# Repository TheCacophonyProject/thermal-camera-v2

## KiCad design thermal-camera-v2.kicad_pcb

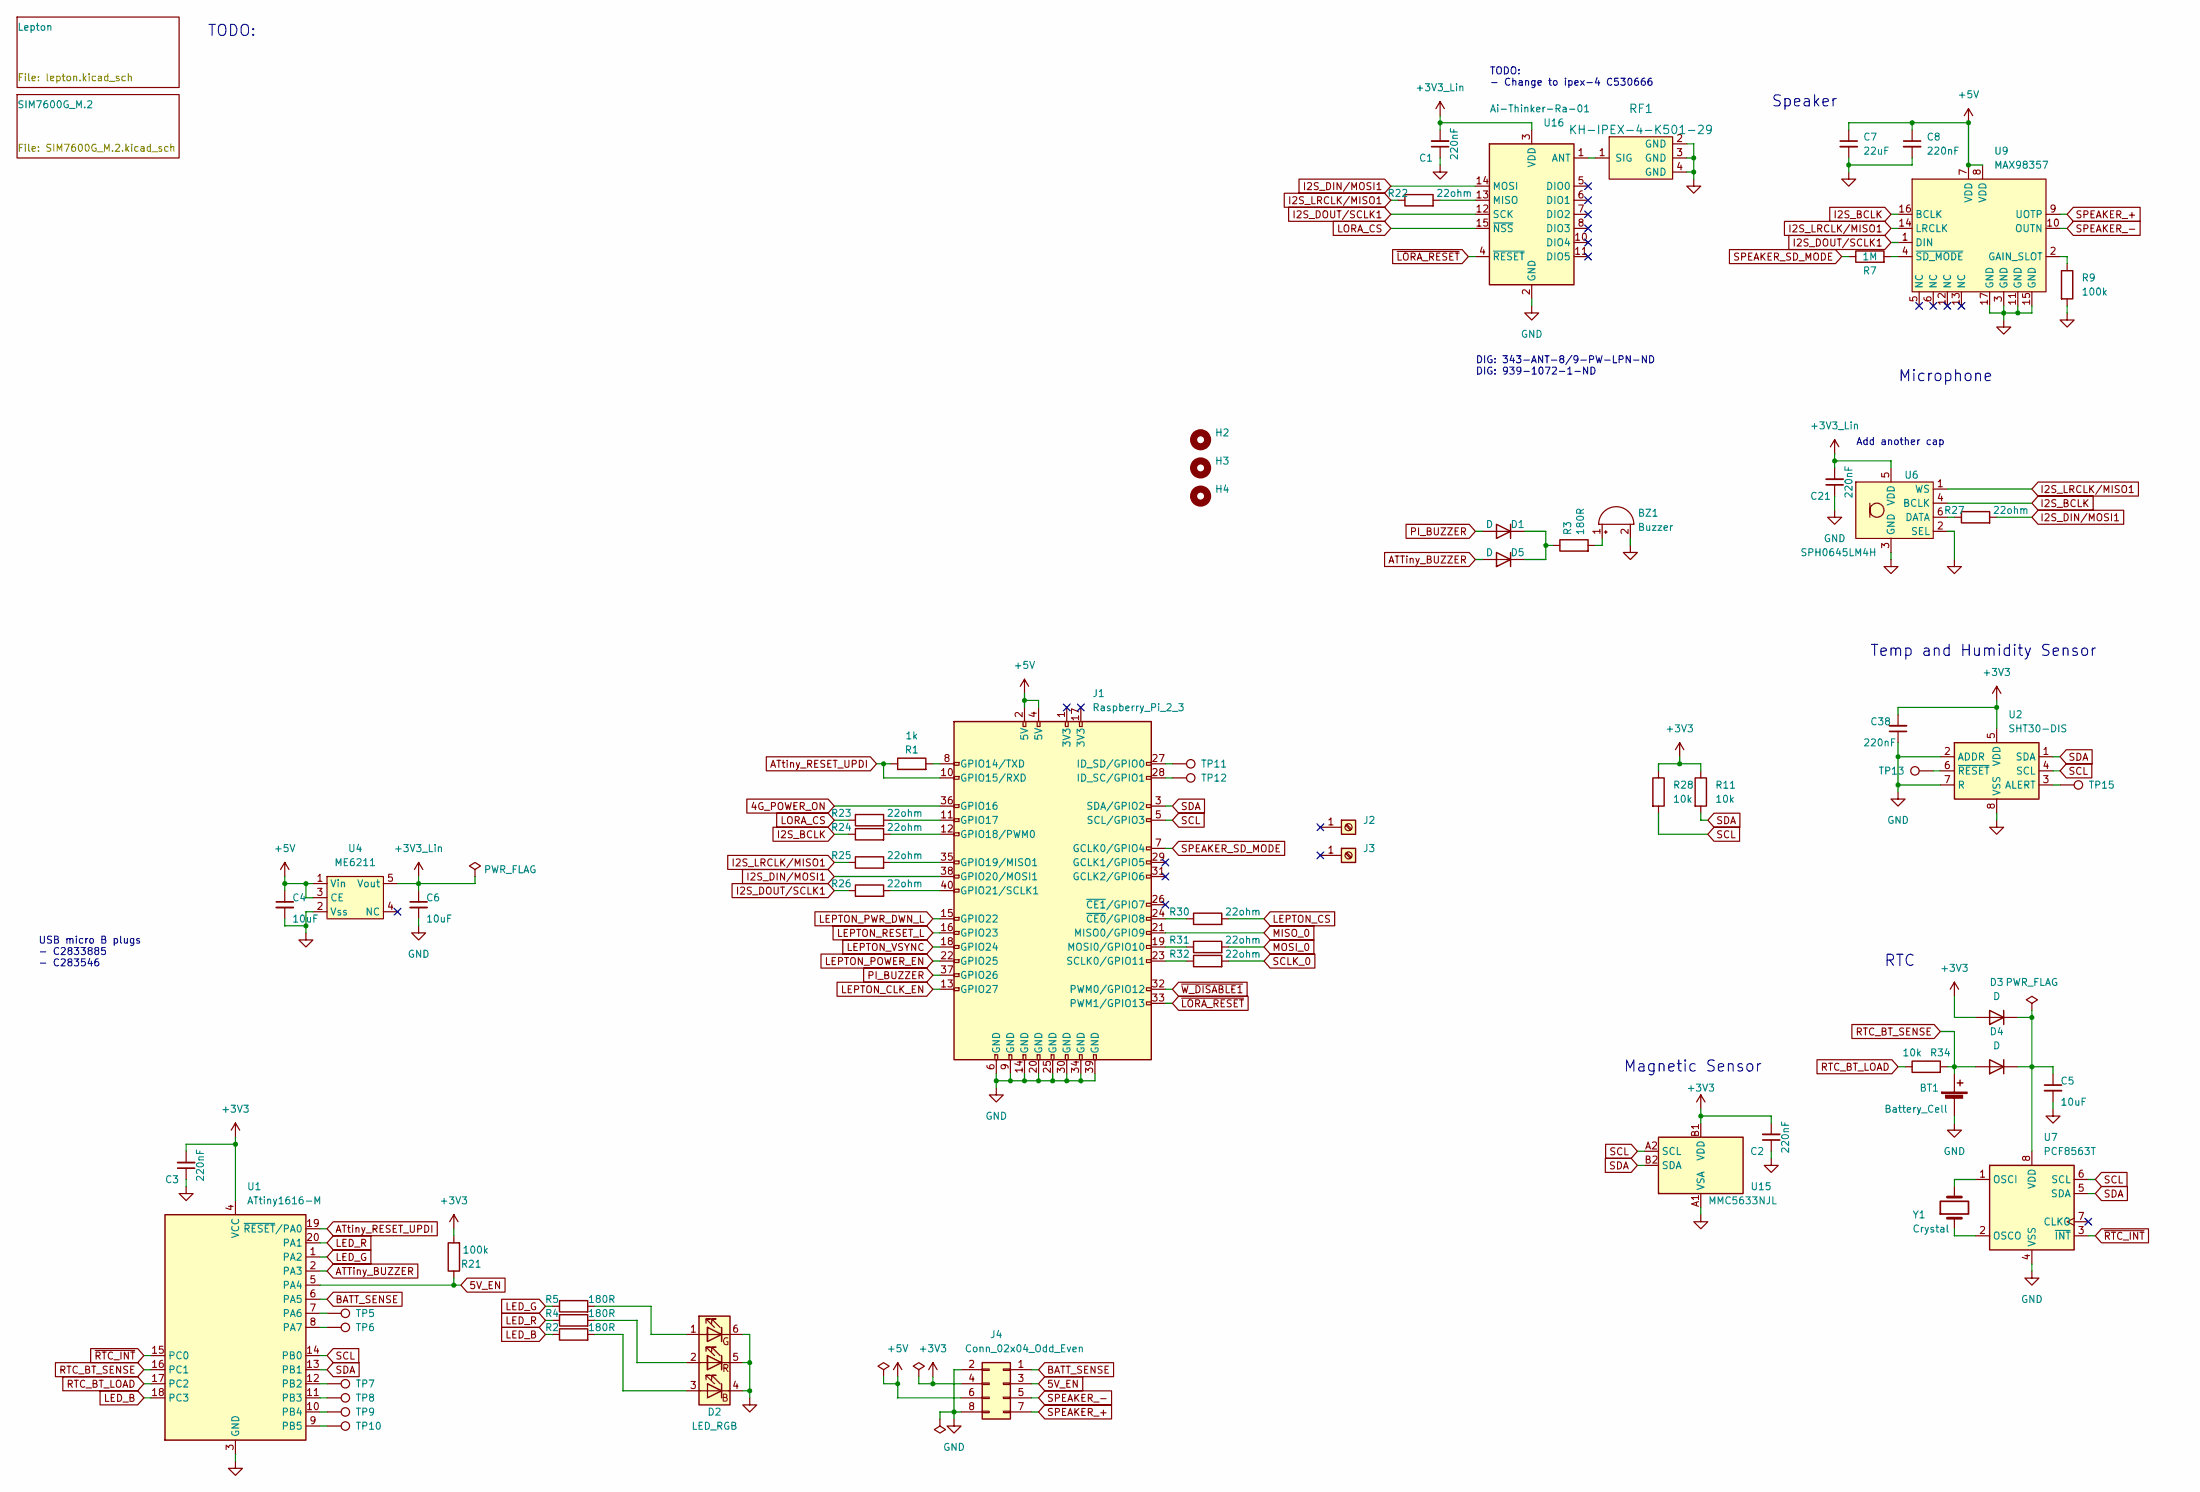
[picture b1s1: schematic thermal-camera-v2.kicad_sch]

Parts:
BT1: Battery_Cell; CR1220; LCSC C969906
BZ1: Buzzer; BUZ-TH_BD9.0-P5.00-D0.6-FD; LCSC C96102
C1, C2, C3, C8, C21, C38: 220nF; C_0402_1005Metric; LCSC C16772
C4, C5, C6: 10uF; C_0603_1608Metric; LCSC C19702
C7: 22uF; C_0603_1608Metric; LCSC C86295
D1, D3, D4, D5: D; D_SOD-523; LCSC C668989
D2: LED_RGB; LED-SMD_6PIN-L1.60-W1.50-BL-RD; LCSC C375568
H2, H3, H4: MountingHole; Mouning_Hole_M3
J1: Raspberry_Pi_2_3; RPi_2_W_SMD; LCSC C3975165
J2, J3: Screw_Terminal_M2_L10; SMD_NUT_D5.6-HD3.6-L10.0; LCSC C2928171
J4: Conn_02x04_Odd_Even; power-pcb; LCSC C124386
R1: 1k; R_0402_1005Metric; LCSC C11702
R2, R3, R4, R5: 180R; R_0402_1005Metric; LCSC C38941
R7: 1M; R_0603_1608Metric; LCSC C22935
R9, R21: 100k; R_0402_1005Metric; LCSC C25741
R11, R28, R34: 10k; R_0402_1005Metric; LCSC C25744
R22, R23, R24, R25, R26, R27, R30, R31, R32: 22ohm; R_0402_1005Metric; LCSC C25092
RF1: KH-IPEX-4-K501-29; IPEX4-SMD_4P-L1.8-W1.7-LS2.0-L_KH-IPEX4-2020; LCSC C530666
TP5, TP6, TP7, TP8, TP9, TP10, TP13, TP15: TestPoint; TP_PAD
TP11, TP12: TestPoint; TP
U1: ATtiny1616-M; VQFN-20-1EP_3x3mm_P0.4mm_EP1.7x1.7mm; LCSC C507118
U2: SHT30-DIS; Sensirion_DFN-8-1EP_2.5x2.5mm_P0.5mm_EP1.1x1.7mm; LCSC C77361
U4: ME6211; SOT-23-5; LCSC C82942
U6: SPH0645LM4H; MIC_SPH0645LM4H-B; LCSC C2686054
U7: PCF8563T; SOIC-8_3.9x4.9mm_P1.27mm; LCSC C7440
U9: MAX98357; TQFN-16-1EP_3x3mm_P0.5mm_EP1.6x1.6mm; LCSC C910544
U15: MMC5633NJL; WLP-4_0.86x0.86mm_P0.4mm; LCSC C404328
U16: Ai-Thinker-Ra-01; WIRELM-SMD_RA-01H; LCSC C503593
Y1: Crystal; Crystal_SMD_3215-2Pin_3.2x1.5mm; LCSC C32346

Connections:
4G_POWER_ON: J1.36 (GPIO16); also elsewhere on the board
5V_EN: J4.3, R21.1, U1.5 (PA4)
+3V3: C2.2, C3.2, C38.2, D3.2 (A), J4.4, R11.1, R21.2, R28.1, U1.4 (VCC), U2.5 (VDD), U15.B1 (VDD); also elsewhere on the board
+3V3_Lin: C1.2, C6.1, C21.2, U4.5 (Vout), U6.5 (VDD), U16.3 (VDD)
+5V: C4.1, C7.1, C8.1, J1.2 (5V), J1.4 (5V), J4.6, U4.1 (Vin), U4.3 (CE), U9.7 (VDD), U9.8 (VDD); also elsewhere on the board
ATTiny_BUZZER: D5.2 (A), U1.2 (PA3)
ATtiny_RESET_UPDI: J1.10 (GPIO15/RXD), R1.1, U1.19 (~RESET/PA0)
BATT_SENSE: J4.1, U1.6 (PA5)
GND: BT1.2 (-), BZ1.2 (+), C1.1, C2.1, C3.1, C4.2, C5.2, C6.2, C7.2, C8.2, C21.1, C38.1, D2.4 (BK), D2.5 (GK), D2.6 (RK), J1.6 (GND), J1.9 (GND), J1.14 (GND), J1.20 (GND), J1.25 (GND), J1.30 (GND), J1.34 (GND), J1.39 (GND), J4.2, J4.8, R9.2, RF1.2 (GND), RF1.3 (GND), RF1.4 (GND), U1.3 (GND), U1.21 (GND), U2.2 (ADDR), U2.7 (R), U2.8 (VSS), U2.9 (VSS), U4.2 (Vss), U6.2 (SEL), U6.3 (GND), U7.4 (VSS), U9.3 (GND), U9.11 (GND), U9.15 (GND), U9.17 (GND), U15.A1 (VSA), U16.2 (GND), U16.9 (GND), U16.16 (GND); also elsewhere on the board
I2S_BCLK: R24.1, U6.4 (BCLK), U9.16 (BCLK)
I2S_DIN/MOSI1: J1.38 (GPIO20/MOSI1), R27.2, U16.14 (MOSI)
I2S_DOUT/SCLK1: R26.1, U9.1 (DIN), U16.12 (SCK)
I2S_LRCLK/MISO1: R22.1, R25.1, U6.1 (WS), U9.14 (LRCLK)
LED_B: R2.1, U1.18 (PC3)
LED_G: R5.1, U1.1 (PA2)
LED_R: R4.1, U1.20 (PA1)
LEPTON_CLK_EN: J1.13 (GPIO27); also elsewhere on the board
LEPTON_CS: R30.2; also elsewhere on the board
LEPTON_POWER_EN: J1.22 (GPIO25); also elsewhere on the board
LEPTON_PWR_DWN_L: J1.15 (GPIO22); also elsewhere on the board
LEPTON_RESET_L: J1.16 (GPIO23); also elsewhere on the board
LEPTON_VSYNC: J1.18 (GPIO24); also elsewhere on the board
LORA_CS: R23.1, U16.15 (~NSS)
MISO_0: J1.21 (MISO0/GPIO9); also elsewhere on the board
MOSI_0: R31.2; also elsewhere on the board
unnamed: BZ1.1 (-), R3.2
unnamed: C5.1, D3.1 (K), D4.1 (K), U7.8 (VDD)
unnamed: D1.1 (K), D5.1 (K), R3.1
unnamed: D2.1 (RA), R5.2
unnamed: D2.2 (GA), R4.2
unnamed: D2.3 (BA), R2.2
unnamed: J1.8 (GPIO14/TXD), R1.2
unnamed: J1.11 (GPIO17), R23.2
unnamed: J1.12 (GPIO18/PWM0), R24.2
unnamed: J1.19 (MOSI0/GPIO10), R31.1
unnamed: J1.23 (SCLK0/GPIO11), R32.1
unnamed: J1.24 (~CE0/GPIO8), R30.1
unnamed: J1.28 (ID_SC/GPIO1), TP12.1
unnamed: J1.35 (GPIO19/MISO1), R25.2
unnamed: J1.40 (GPIO21/SCLK1), R26.2
unnamed: R7.2, U9.4 (~SD_MODE)
unnamed: R9.1, U9.2 (GAIN_SLOT)
unnamed: R22.2, U16.13 (MISO)
unnamed: R27.1, U6.6 (DATA)
unnamed: RF1.1 (SIG), U16.1 (ANT)
unnamed: J1.27 (ID_SD/GPIO0), TP11.1
unnamed: TP5.1, U1.7 (PA6)
unnamed: TP6.1, U1.8 (PA7)
unnamed: TP10.1, U1.9 (PB5)
unnamed: TP9.1, U1.10 (PB4)
unnamed: TP8.1, U1.11 (PB3)
unnamed: TP7.1, U1.12 (PB2)
unnamed: TP15.1, U2.3 (ALERT)
unnamed: TP13.1, U2.6 (~RESET)
unnamed: U7.1 (OSCI), Y1.2
unnamed: U7.2 (OSCO), Y1.1
PI_BUZZER: D1.2 (A), J1.37 (GPIO26)
RTC_BT_LOAD: R34.1, U1.17 (PC2)
RTC_BT_SENSE: BT1.1 (+), D4.2 (A), R34.2, U1.16 (PC1)
SCL: J1.5 (SCL/GPIO3), R28.2, U1.14 (PB0), U2.4 (SCL), U7.6 (SCL), U15.A2 (SCL); also elsewhere on the board
SCLK_0: R32.2; also elsewhere on the board
SDA: J1.3 (SDA/GPIO2), R11.2, U1.13 (PB1), U2.1 (SDA), U7.5 (SDA), U15.B2 (SDA); also elsewhere on the board
SPEAKER_+: J4.7, U9.9 (UOTP)
SPEAKER_-: J4.5, U9.10 (OUTN)
SPEAKER_SD_MODE: J1.7 (GCLK0/GPIO4), R7.1
~LORA_RESET: J1.33 (PWM1/GPIO13), U16.4 (~RESET)
~RTC_INT: U1.15 (PC0), U7.3 (~INT)
~W_DISABLE1: J1.32 (PWM0/GPIO12); also elsewhere on the board

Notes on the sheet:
Magnetic Sensor
Add another cap
Speaker
USB micro B plugs - C2833885 - C283546
TODO: - Change to ipex-4 C530666
Microphone
TODO:
DIG: 343-ANT-8/9-PW-LPN-ND DIG: 939-1072-1-ND
Temp and Humidity Sensor
RTC

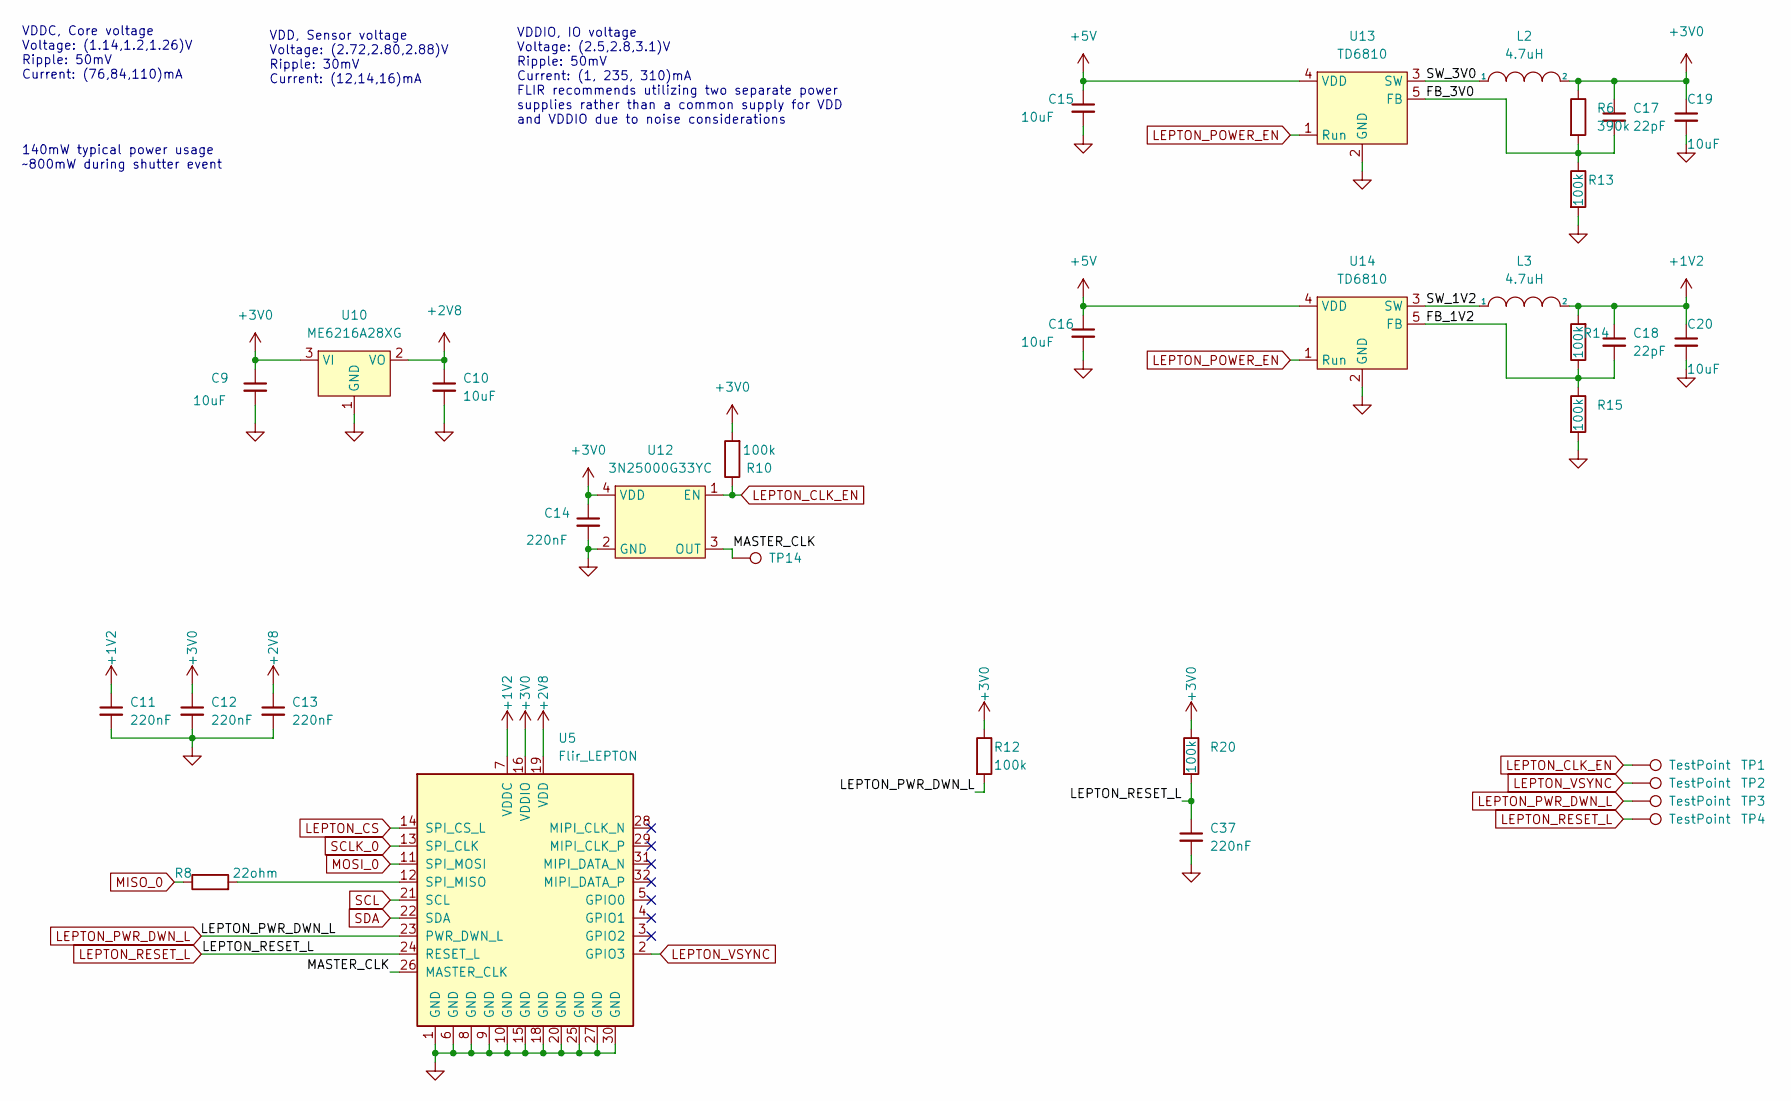
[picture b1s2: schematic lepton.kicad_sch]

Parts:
C9, C10, C15, C16, C19, C20: 10uF; C_0603_1608Metric; LCSC C19702
C11, C12, C13, C14, C37: 220nF; C_0402_1005Metric; LCSC C16772
C17, C18: 22pF; C_0402_1005Metric; LCSC C1555
L2, L3: 4.7uH; IND-SMD_L4.0-W4.0_SWPA4018S; LCSC C354574
R6: 390k; R_0402_1005Metric; LCSC C2943536
R8: 22ohm; R_0402_1005Metric; LCSC C25092
R10: 100k; R_0402_1005Metric; MPN RC1005F103CS; LCSC C25741
R12, R13, R14, R15, R20: 100k; R_0402_1005Metric; LCSC C25741
TP1, TP2, TP3, TP4, TP14: TestPoint; TP
U5: Flir_LEPTON; MOLEX_105028-1001; MPN 1050281001; LCSC C585422
U10: ME6216A28XG; TSOT-23; LCSC C427601
U12: 3N25000G33YC; OSC-SMD_4P-L3.2-W2.5-BL; LCSC C252341
U13, U14: TD6810; TSOT-23-5; LCSC C16510

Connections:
+1V2: C11.1, C18.1, C20.1, L3.2, R14.2, U5.7 (VDDC)
+2V8: C10.1, C13.1, U5.19 (VDD), U10.2 (VO)
+3V0: C9.1, C12.1, C14.1, C17.1, C19.1, L2.2, R6.1, R10.2, R12.1, R20.1, U5.16 (VDDIO), U10.3 (VI), U12.4 (VDD)
+5V: C15.1, C16.1, U13.4 (VDD), U14.4 (VDD); also elsewhere on the board
/Lepton/FB_1V2: C18.2, R14.1, R15.1, U14.5 (FB)
/Lepton/FB_3V0: C17.2, R6.2, R13.1, U13.5 (FB)
/Lepton/MASTER_CLK: TP14.1, U5.26 (MASTER_CLK), U12.3 (OUT)
/Lepton/SW_1V2: L3.1, U14.3 (SW)
/Lepton/SW_3V0: L2.1, U13.3 (SW)
GND: C9.2, C10.2, C11.2, C12.2, C13.2, C14.2, C15.2, C16.2, C19.2, C20.2, C37.2, R13.2, R15.2, U5.1 (GND), U5.6 (GND), U5.8 (GND), U5.9 (GND), U5.10 (GND), U5.15 (GND), U5.18 (GND), U5.20 (GND), U5.25 (GND), U5.27 (GND), U5.30 (GND), U10.1 (GND), U12.2 (GND), U13.2 (GND), U14.2 (GND); also elsewhere on the board
LEPTON_CLK_EN: R10.1, TP1.1, U12.1 (EN); also elsewhere on the board
LEPTON_CS: U5.14 (SPI_CS_L); also elsewhere on the board
LEPTON_POWER_EN: U13.1 (Run), U14.1 (Run); also elsewhere on the board
LEPTON_PWR_DWN_L: R12.2, TP3.1, U5.23 (PWR_DWN_L); also elsewhere on the board
LEPTON_RESET_L: C37.1, R20.2, TP4.1, U5.24 (RESET_L); also elsewhere on the board
LEPTON_VSYNC: TP2.1, U5.2 (GPIO3); also elsewhere on the board
MISO_0: R8.1; also elsewhere on the board
MOSI_0: U5.11 (SPI_MOSI); also elsewhere on the board
unnamed: R8.2, U5.12 (SPI_MISO)
SCL: U5.21 (SCL); also elsewhere on the board
SCLK_0: U5.13 (SPI_CLK); also elsewhere on the board
SDA: U5.22 (SDA); also elsewhere on the board

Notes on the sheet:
VDD, Sensor voltage Voltage: (2.72,2.80,2.88)V Ripple: 30mV Current: (12,14,16)mA
VDDIO, IO voltage Voltage: (2.5,2.8,3.1)V Ripple: 50mV Current: (1, 235, 310)mA FLIR recommends utilizing two separate power supplies rather than a common supply for VDD and VDDIO due to noise considerations
VDDC, Core voltage Voltage: (1.14,1.2,1.26)V Ripple: 50mV Current: (76,84,110)mA
140mW typical power usage ~800mW during shutter event

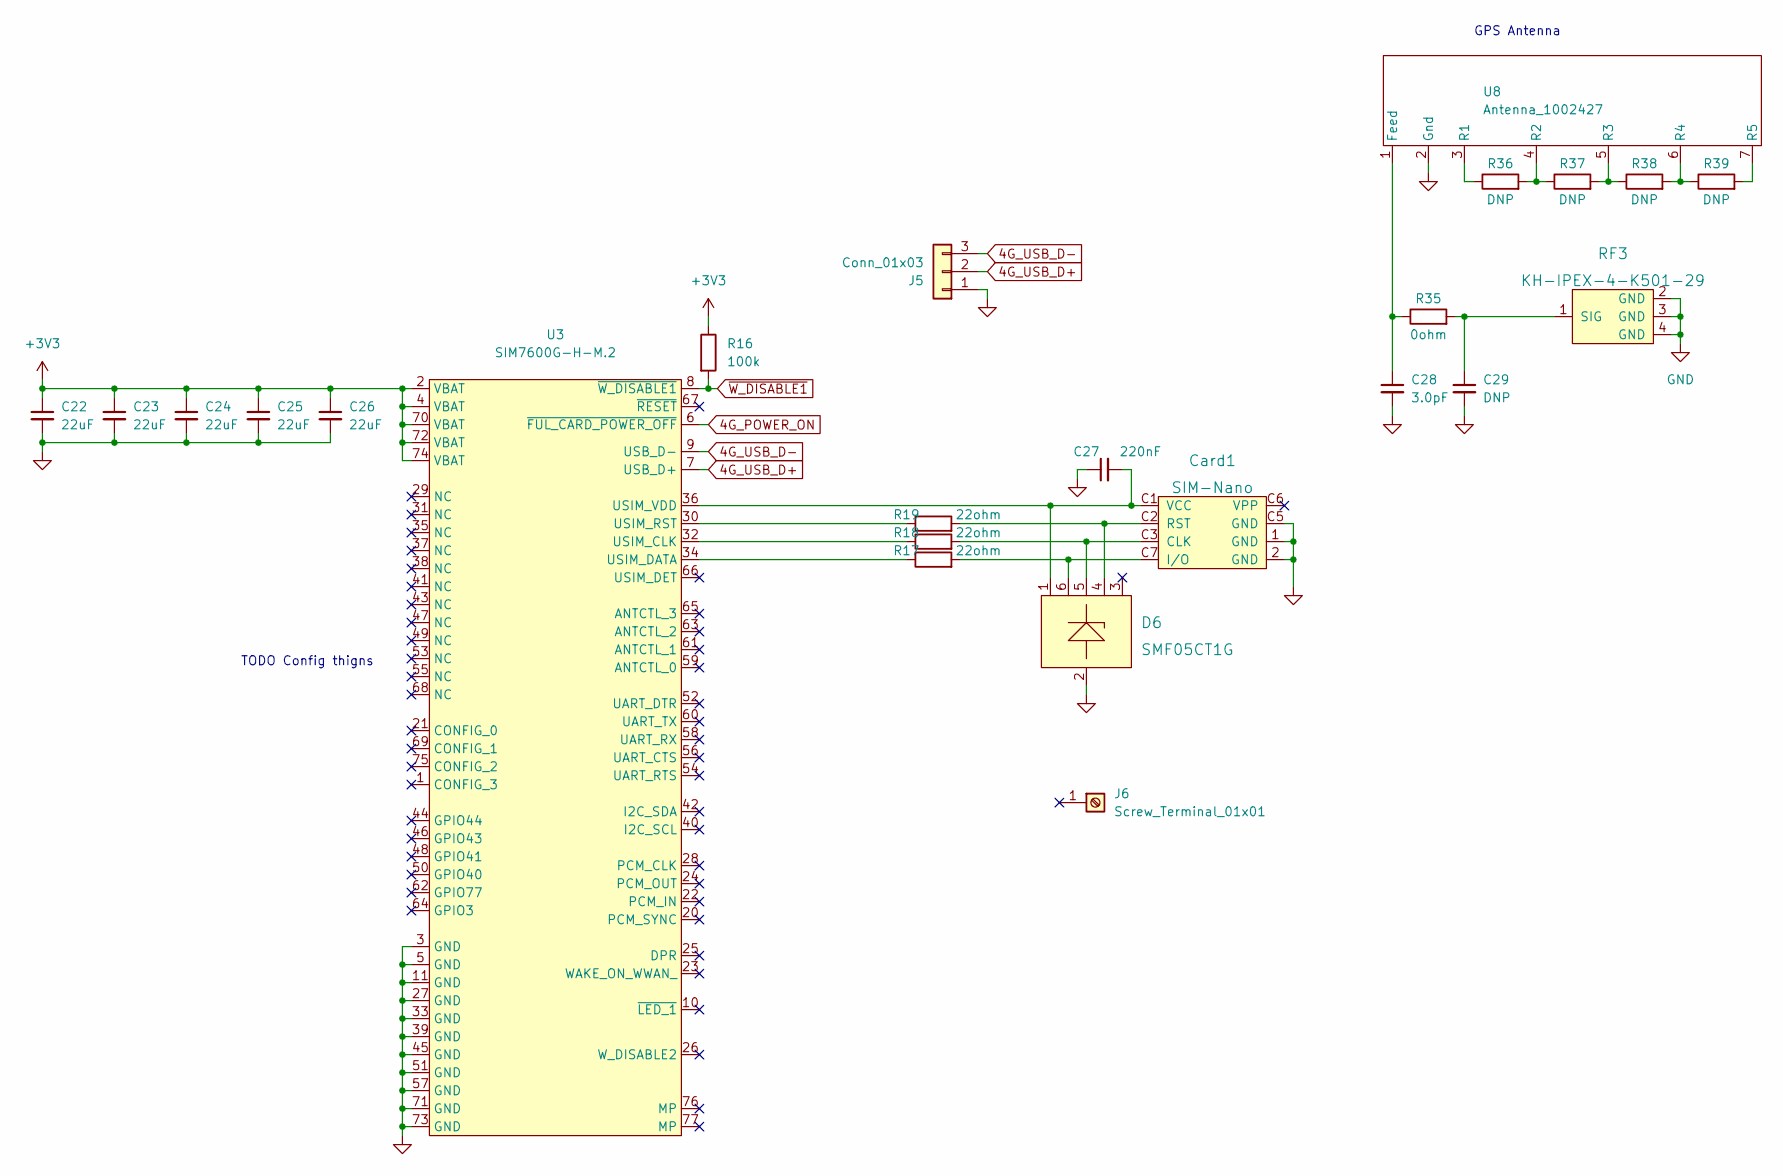
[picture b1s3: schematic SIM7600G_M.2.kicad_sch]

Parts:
C22, C23, C24, C25, C26: 22uF; C_0603_1608Metric; LCSC C86295
C27: 220nF; C_0402_1005Metric; LCSC C16772
C28: 3.0pF; C_0402_1005Metric; LCSC C318583
C29: DNP; C_0402_1005Metric; LCSC C76903
Card1: SIM-Nano; LCSC C266889
D6: SMF05CT1G; SOT-363_L2.0-W1.3-P0.65-LS2.1-TL; LCSC C15879
J5: Conn_01x03; PinHeader_1x03_P2.54mm_Vertical
J6: Screw_Terminal_01x01; SMD_BD4.4-L4.4-D2.8; LCSC C2928178
R16: 100k; R_0402_1005Metric; LCSC C25741
R17, R18, R19: 22ohm; R_0402_1005Metric; LCSC C25092
R35: 0ohm; R_0402_1005Metric; LCSC C17168
R36, R37, R38, R39: DNP; R_0402_1005Metric
RF3: KH-IPEX-4-K501-29; IPEX4-SMD_4P-L1.8-W1.7-LS2.0-L_KH-IPEX4-2020; LCSC C530666
U3: SIM7600G-H-M.2; M.2; LCSC C2761526
U8: Antenna_1002427; ANTENNA_1002427_GPS

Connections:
4G_POWER_ON: U3.6 (~FUL_CARD_POWER_OFF); also elsewhere on the board
4G_USB_D+: J5.2, U3.7 (USB_D+)
4G_USB_D-: J5.3, U3.9 (USB_D-)
+3V3: C22.1, C23.1, C24.1, C25.1, C26.1, R16.1, U3.2 (VBAT), U3.4 (VBAT), U3.70 (VBAT), U3.72 (VBAT), U3.74 (VBAT); also elsewhere on the board
GND: C22.2, C23.2, C24.2, C25.2, C26.2, C27.1, C28.2, C29.2, Card1.1 (GND), Card1.2 (GND), Card1.C5 (GND), D6.2, J5.1, RF3.2 (GND), RF3.3 (GND), RF3.4 (GND), U3.3 (GND), U3.5 (GND), U3.11 (GND), U3.27 (GND), U3.33 (GND), U3.39 (GND), U3.45 (GND), U3.51 (GND), U3.57 (GND), U3.71 (GND), U3.73 (GND), U8.2 (Gnd); also elsewhere on the board
unnamed: C27.2, Card1.C1 (VCC), D6.1, U3.36 (USIM_VDD)
unnamed: C28.1, R35.1, U8.1 (Feed)
unnamed: C29.1, R35.2, RF3.1 (SIG)
unnamed: Card1.C3 (CLK), D6.5, R18.2
unnamed: Card1.C7 (I/O), D6.6, R17.2
unnamed: R18.1, U3.32 (USIM_CLK)
unnamed: Card1.C2 (RST), D6.4, R19.2
unnamed: R36.1, U8.3 (R1)
unnamed: R36.2, R37.1, U8.4 (R2)
unnamed: R37.2, R38.1, U8.5 (R3)
unnamed: R38.2, R39.1, U8.6 (R4)
unnamed: R39.2, U8.7 (R5)
unnamed: R19.1, U3.30 (USIM_RST)
unnamed: R17.1, U3.34 (USIM_DATA)
~W_DISABLE1: R16.2, U3.8 (~W_DISABLE1); also elsewhere on the board

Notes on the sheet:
GPS Antenna
TODO Config thigns

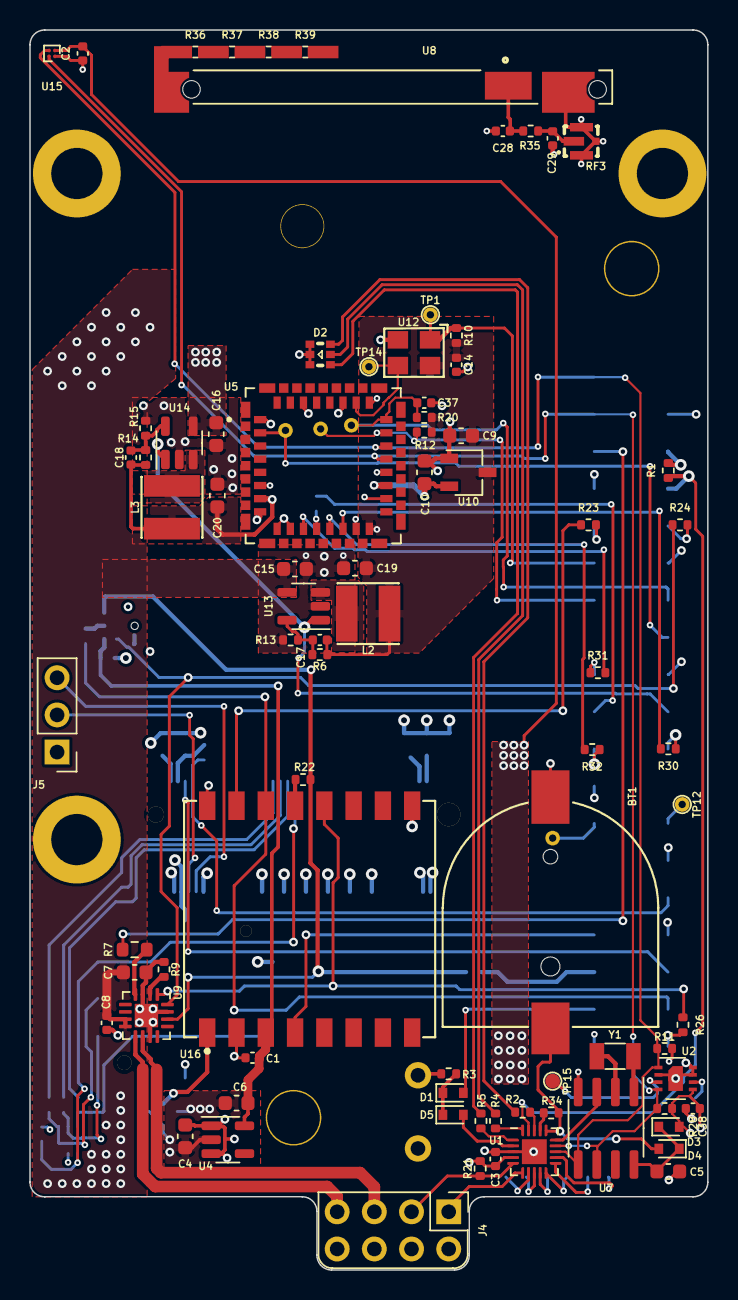
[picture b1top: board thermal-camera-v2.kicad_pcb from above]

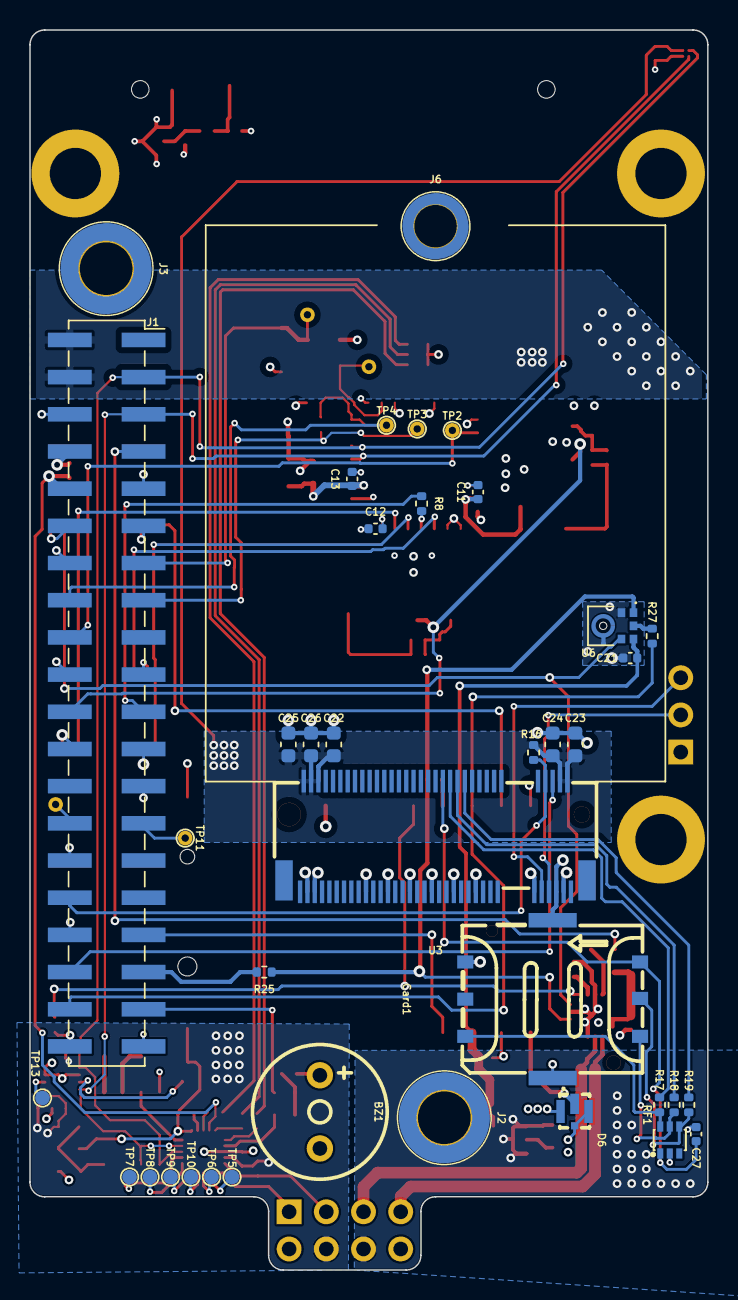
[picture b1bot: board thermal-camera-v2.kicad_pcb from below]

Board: 4 copper layers, 46.3 x 84.7 mm, 121 parts (38 on the bottom side), 93 nets.

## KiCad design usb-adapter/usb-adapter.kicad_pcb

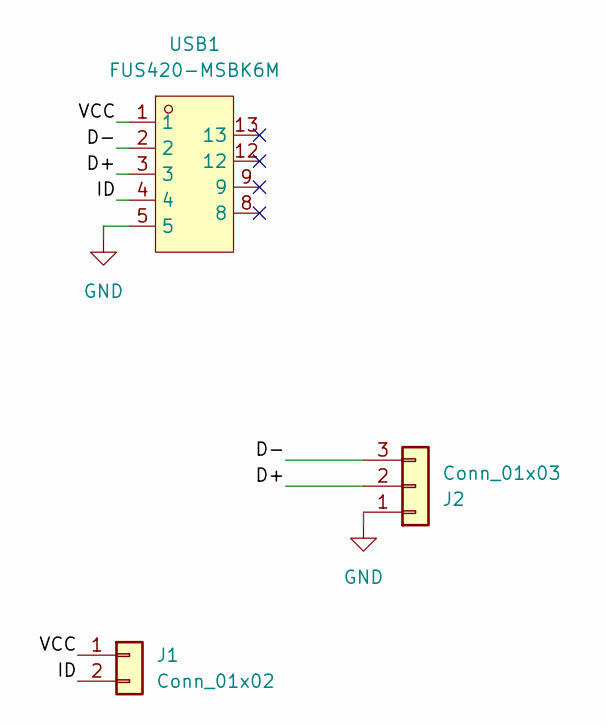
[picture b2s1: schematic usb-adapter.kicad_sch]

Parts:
J1: Conn_01x02; PinSocket_1x02_P2.54mm_Vertical
J2: Conn_01x03; PinSocket_1x03_P2.54mm_Vertical
USB1: FUS420-MSBK6M; MICRO-USB-SMD_FUS420-MSBK6M; LCSC Part C2833885

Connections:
/D+: J2.2, USB1.3
/D-: J2.3, USB1.2
/ID: J1.2, USB1.4
/VCC: J1.1, USB1.1
GND: J2.1, USB1.5

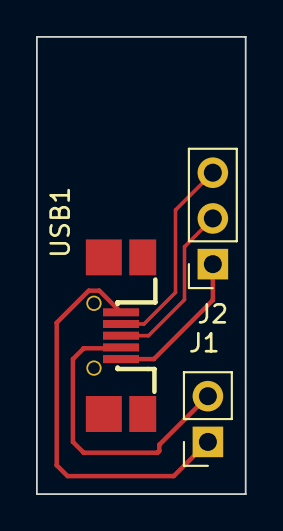
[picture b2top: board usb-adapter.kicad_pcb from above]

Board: 2 copper layers, 11.6 x 25.4 mm, 3 parts (0 on the bottom side), 5 nets.
